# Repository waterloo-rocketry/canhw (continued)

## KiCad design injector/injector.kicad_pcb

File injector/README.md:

# Injector Board

This board is responsible for opening and closing the valve that allows for the nitrous oxide to flow into the engine before launch. It is designed to be able to deliver 10A of current to the injector valve. Limit switches mounted on the valve allow valve state to be determined.

The injector board is connected to the rocket CAN bus, through which it receives commands. The state of the injector valve is broadcast through the bus. The logic part of the board is powered from the bus, while the valve control portion is powered by an external lithium polymer battery.

## Front:

## Back:

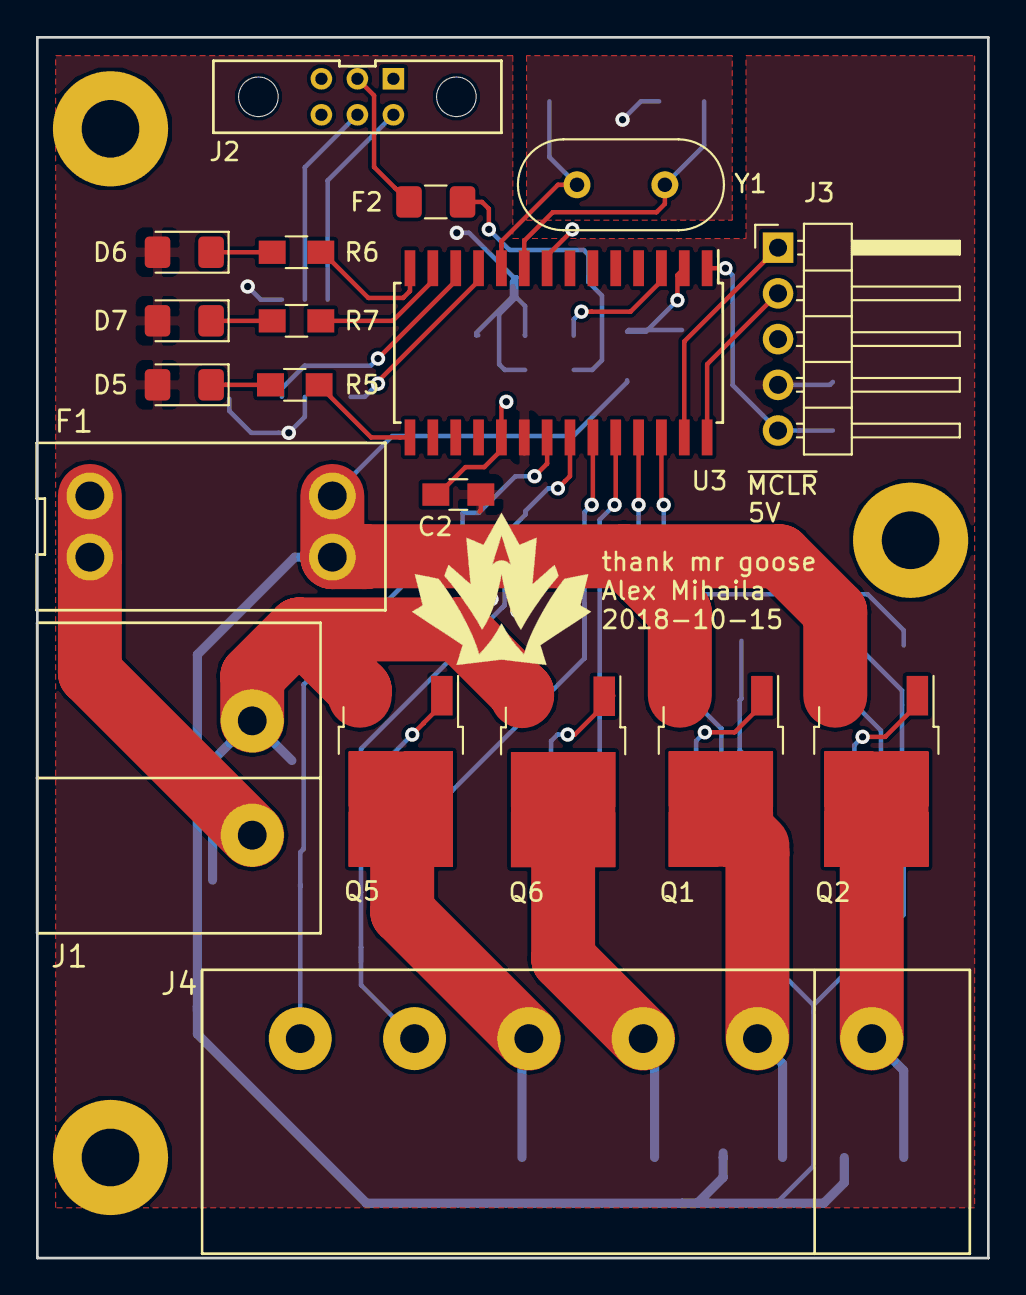
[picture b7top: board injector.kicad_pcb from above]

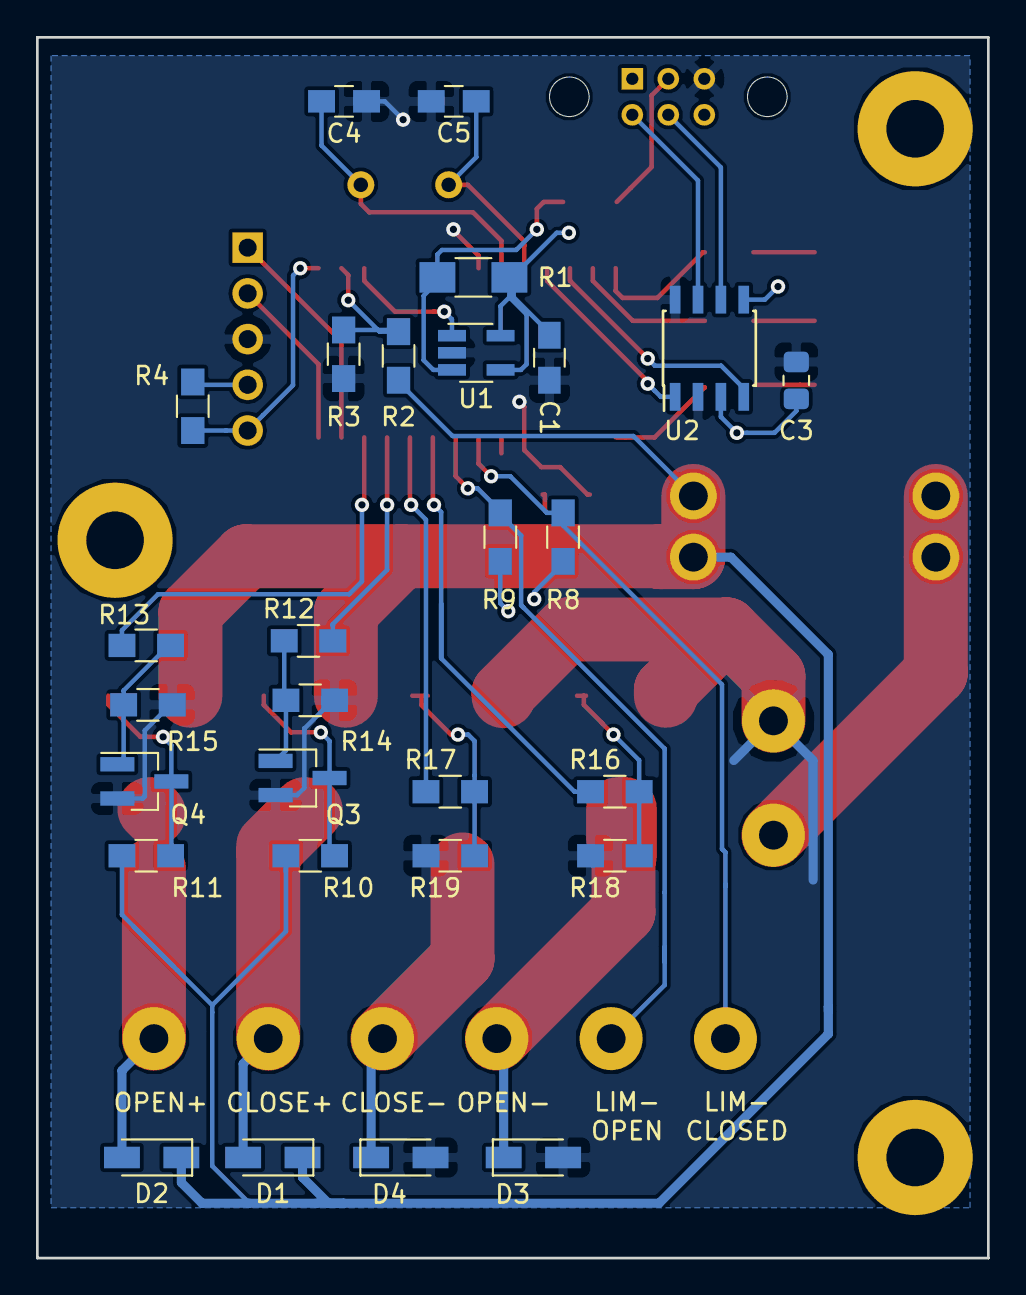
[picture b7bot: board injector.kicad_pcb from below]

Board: 2 copper layers, 52.8 x 67.8 mm, 47 parts (28 on the bottom side), 39 nets.

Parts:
C1, C2: 0.1uF; C_0805_HandSoldering
C3: 10uF; C_0805_2012Metric_Pad1.15x1.40mm_HandSolder
C4, C5: 26pF; C_0805_HandSoldering
D1, D2, D3, D4: BAS16GWJ; D_SOD-123_HandSoldering
D5, D6, D7: LED; LED_1206_3216Metric_Pad1.42x1.75mm_HandSolder
F1: 30A; PC_AutoFuse_Holder
F2: Polyfuse; Fuse_1206_3216Metric_Pad1.42x1.75mm_HandSolder
J1: Valve Power; Barrier_Strip_2Circuit
J2: CAN Connector; connector_Harwin_M80-5000642
J3: Programming Header; Pin_Header_Angled_1x05_Pitch2.54mm
J4: Valve Control; Barrier_Strip_6Circuit
Q1, Q2: AOD417; TO-252-2
Q3, Q4: DMG2302UK; SOT-23_Handsoldering
Q5, Q6: AOD476; TO-252-2
R1: 200mR; R_1206_HandSoldering
R2: 27K; R_0805_HandSoldering
R3, R4, R8, R9, R14, R15, R18, R19: 10K; R_0805_HandSoldering
R5, R6, R7: 330R; R_0805_HandSoldering
R10, R11: 15K; R_0805_HandSoldering
R12, R13, R16, R17: 270R; R_0805_HandSoldering
U1: INA180; SOT-23-5_HandSoldering
U2: MCP2562; SOIC-8_3.9x4.9mm_Pitch1.27mm
U3: PIC18F26K83; SOIC-28W_7.5x17.9mm_Pitch1.27mm
Y1: Crystal; Crystal_HC49-4H_Vertical

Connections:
+5V: C1.2, C2.2, C3.1, D5.2, D6.2, D7.2, J3.4, R1.1, R4.1, R8.1, R9.1, U1.4, U1.5, U2.3, U2.5, U3.20
+BATT: D1.1, D2.1, F1.2, Q1.3, Q2.3, R2.1, R10.1, R11.1
/MCU/CAN_RX: U2.4, U3.12
/MCU/CAN_TX: U2.1, U3.11
/MCU/CURR_AMP: U1.1, U3.3
/MCU/HIGH_SIDE_A: R12.2, U3.25
/MCU/HIGH_SIDE_B: R13.1, U3.26
/MCU/ICSPCLK: J3.1, U3.27
/MCU/ICSPDAT: J3.2, U3.28
/MCU/LIM_CLOSE: J4.6, R8.2, U3.21
/MCU/LIM_OPEN: J4.5, R9.2, U3.22
/MCU/LOW_SIDE_A: R16.2, U3.23
/MCU/LOW_SIDE_B: R17.1, U3.24
/MCU/OSC1: C4.1, U3.9, Y1.1
/MCU/OSC2: C5.1, U3.10, Y1.2
/MCU/VBAT: R2.2, R3.1, U3.2
/MCU/~MCLR: J3.5, R4.2, U3.1
/Motor Control/CLOSE+: D1.2, J4.2, Q1.2
/Motor Control/CLOSE-: D4.1, J4.3, Q6.2
/Motor Control/OPEN+: D2.2, J4.1, Q2.2
/Motor Control/OPEN-: D3.1, J4.4, Q5.2
CANH: J2.4, U2.7
CANL: J2.5, U2.6
GND: C1.1, C2.1, C3.2, C4.2, C5.2, D3.2, D4.2, J1.2, J2.3, J3.3, Q3.2, Q4.2, Q5.3, Q6.3, R3.2, R14.2, R15.2, R18.2, R19.2, U1.2, U2.2, U2.8, U3.8, U3.19
unnamed: D5.1, R5.1
unnamed: D6.1, R6.1
unnamed: D7.1, R7.1
unnamed: F1.1, J1.1
unnamed: F2.1, R1.2, U1.3
unnamed: F2.2, J2.2
unnamed: Q1.1, Q3.3, R10.2
unnamed: Q2.1, Q4.3, R11.2
unnamed: Q3.1, R12.1, R14.1
unnamed: Q4.1, R13.2, R15.1
unnamed: Q5.1, R16.1, R18.1
unnamed: Q6.1, R17.2, R19.1
unnamed: R5.2, U3.15
unnamed: R6.2, U3.14
unnamed: R7.2, U3.13

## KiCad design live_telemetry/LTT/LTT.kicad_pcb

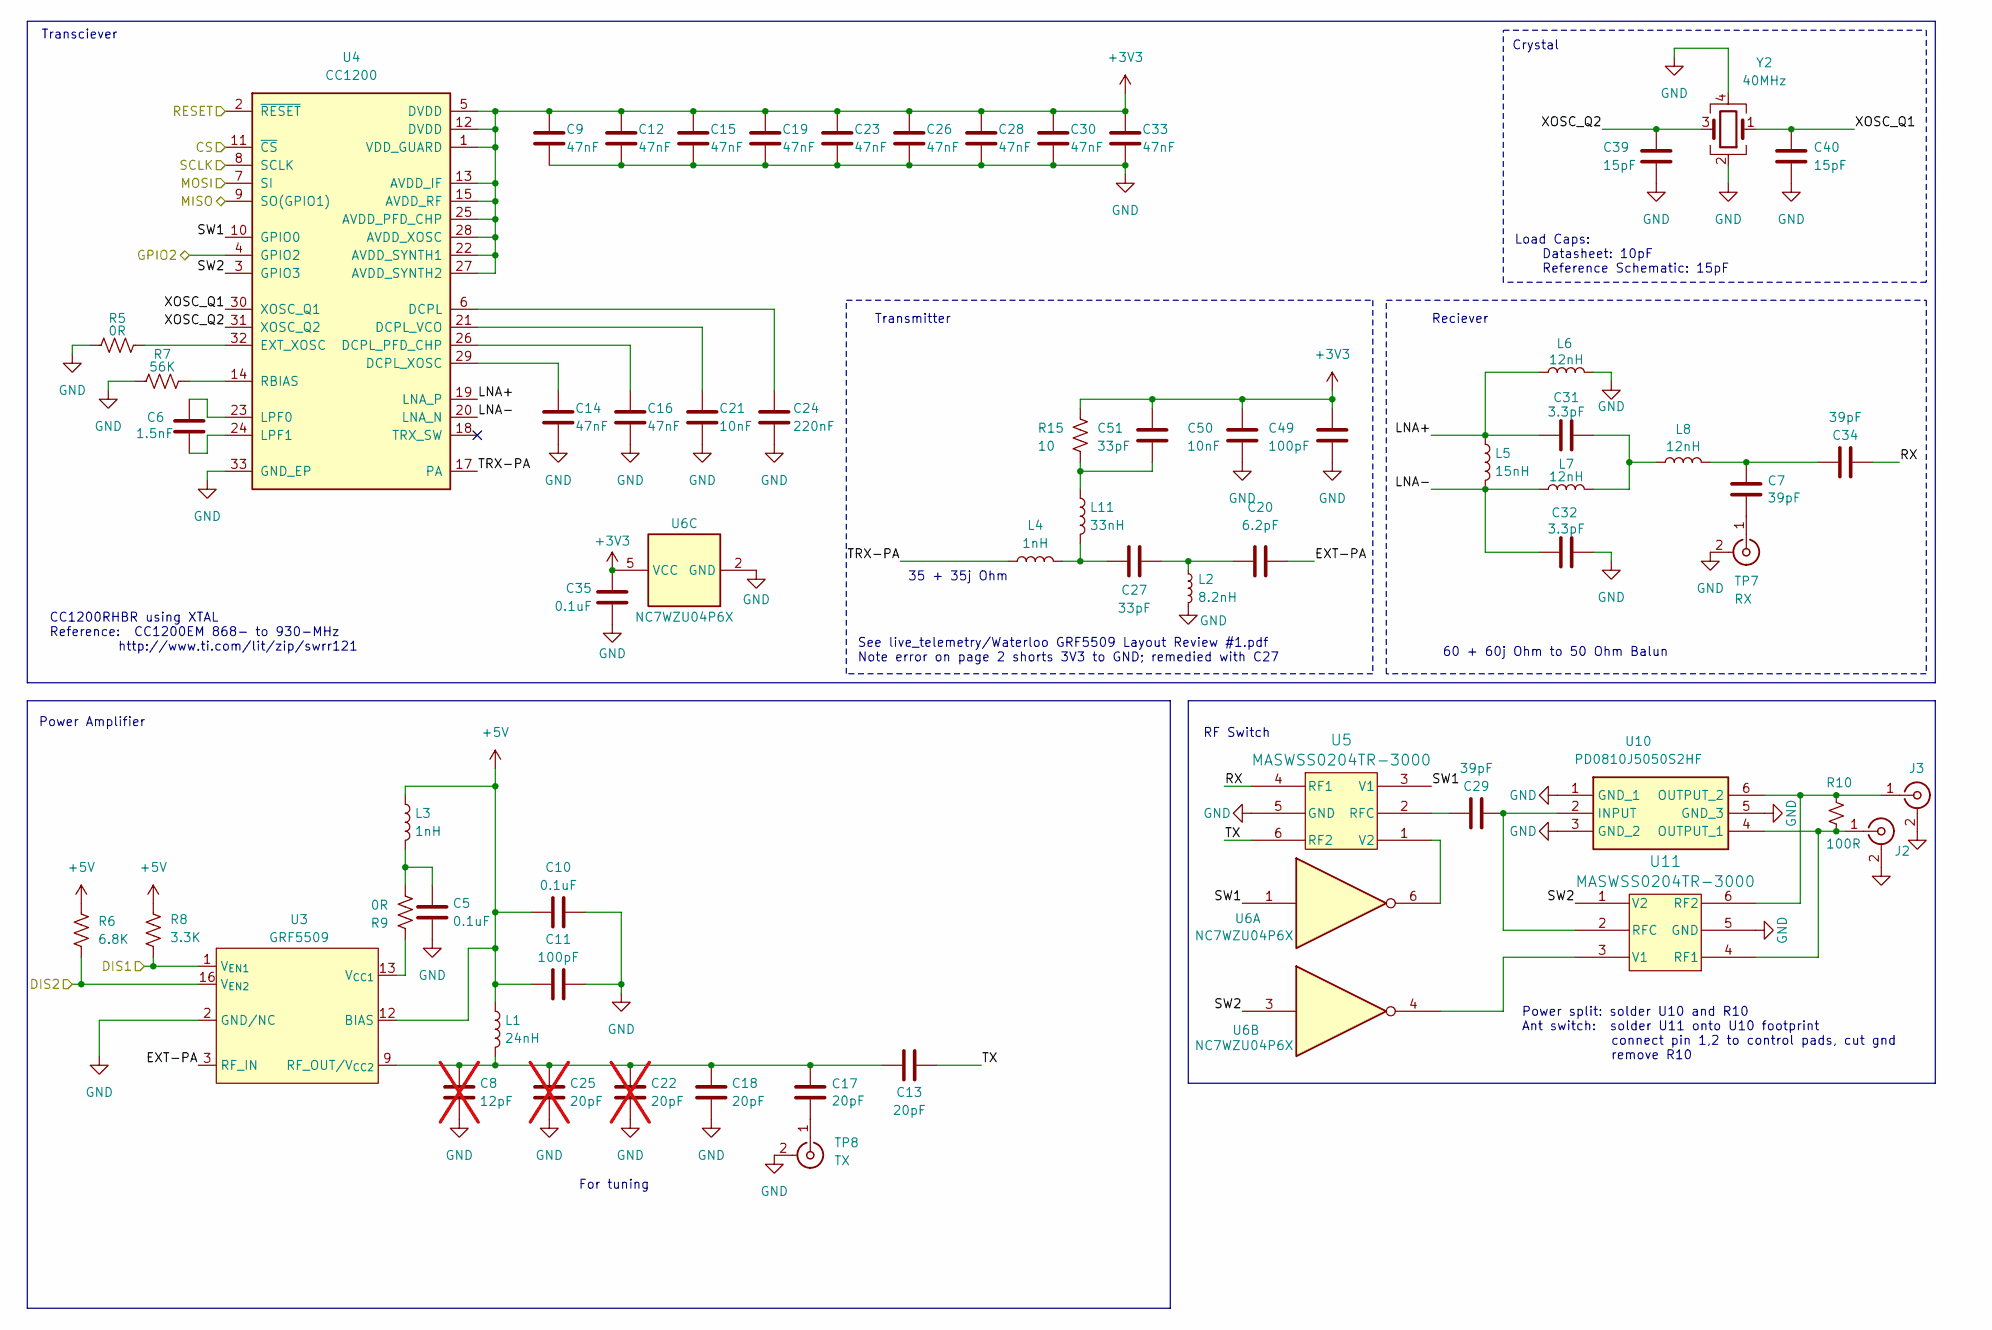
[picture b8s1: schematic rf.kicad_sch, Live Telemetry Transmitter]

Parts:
C5, C10, C35: 0.1uF; C_0402_1005Metric_Pad0.74x0.62mm_HandSolder
C6: 1.5nF; C_0402_1005Metric_Pad0.74x0.62mm_HandSolder
C7, C29, C34: 39pF; C_0402_1005Metric_Pad0.74x0.62mm_HandSolder
C8: 12pF; C_0402_1005Metric_Pad0.74x0.62mm_HandSolder; not fitted
C9, C12, C14, C15, C16, C19, C23, C26, C28, C30, C33: 47nF; C_0402_1005Metric_Pad0.74x0.62mm_HandSolder
C11, C49: 100pF; C_0402_1005Metric_Pad0.74x0.62mm_HandSolder
C13, C17, C18: 20pF; C_0402_1005Metric_Pad0.74x0.62mm_HandSolder
C20: 6.2pF; C_0402_1005Metric_Pad0.74x0.62mm_HandSolder
C21, C50: 10nF; C_0402_1005Metric_Pad0.74x0.62mm_HandSolder
C22, C25: 20pF; C_0402_1005Metric_Pad0.74x0.62mm_HandSolder; not fitted
C24: 220nF; C_0402_1005Metric_Pad0.74x0.62mm_HandSolder
C27, C51: 33pF; C_0402_1005Metric_Pad0.74x0.62mm_HandSolder
C31, C32: 3.3pF; C_0402_1005Metric_Pad0.74x0.62mm_HandSolder
C39, C40: 15pF; C_0402_1005Metric_Pad0.74x0.62mm_HandSolder
J2, J3: Conn_Coaxial; SMA_Samtec_SMA-J-P-H-ST-EM1_EdgeMount
L1: 24nH; L_0402_1005Metric_Pad0.77x0.64mm_HandSolder
L2: 8.2nH; L_0402_1005Metric_Pad0.77x0.64mm_HandSolder
L3, L4: 1nH; L_0402_1005Metric_Pad0.77x0.64mm_HandSolder
L5: 15nH; L_0402_1005Metric_Pad0.77x0.64mm_HandSolder
L6, L7, L8: 12nH; L_0402_1005Metric_Pad0.77x0.64mm_HandSolder
L11: 33nH; L_0402_1005Metric_Pad0.77x0.64mm_HandSolder
R5, R9: 0R; R_0402_1005Metric_Pad0.72x0.64mm_HandSolder
R6: 6.8K; R_0402_1005Metric_Pad0.72x0.64mm_HandSolder
R7: 56K; R_0402_1005Metric_Pad0.72x0.64mm_HandSolder
R8: 3.3K; R_0402_1005Metric_Pad0.72x0.64mm_HandSolder
R10: 100R; R_0603_1608Metric_Pad0.98x0.95mm_HandSolder
R15: 10; R_0402_1005Metric_Pad0.72x0.64mm_HandSolder
TP7: RX; U.FL_Molex_MCRF_73412-0110_Vertical
TP8: TX; U.FL_Molex_MCRF_73412-0110_Vertical
U3: GRF5509; QFN50P300X300X85-17N
U4: CC1200; QFN-32-1EP_5x5mm_P0.5mm_EP3.45x3.45mm
U5, U11: MASWSS0204TR-3000; SOT-363_1P25X2_MCM
U6: NC7WZU04P6X; SOT-363_SC-70-6_Handsoldering
U10: PD0810J5050S2HF; Manufacturer_Part_Number PD0810J5050S2HF
Y2: 40MHz; Crystal_SMD_3225-4Pin_3.2x2.5mm

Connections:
+3V3: C9.1, C12.1, C15.1, C19.1, C23.1, C26.1, C28.1, C30.1, C33.1, C35.1, C49.1, C50.1, C51.1, R15.1, U4.1 (VDD_GUARD), U4.5 (DVDD), U4.12 (DVDD), U4.13 (AVDD_IF), U4.15 (AVDD_RF), U4.22 (AVDD_SYNTH1), U4.25 (AVDD_PFD_CHP), U4.27 (AVDD_SYNTH2), U4.28 (AVDD_XOSC), U6.5 (VCC); also elsewhere on the board
+5V: C10.1, C11.1, L1.1, L3.1, R6.1, R8.1, U3.12 (BIAS); also elsewhere on the board
/MCU/CS: U4.11 (~CS); also elsewhere on the board
/MCU/DIS1: R8.2, U3.1 (V_{EN1}); also elsewhere on the board
/MCU/DIS2: R6.2, U3.16 (V_{EN2}); also elsewhere on the board
/MCU/GPIO2: U4.4 (GPIO2); also elsewhere on the board
/MCU/MISO: U4.9 (SO(GPIO1)); also elsewhere on the board
/MCU/MOSI: U4.7 (SI); also elsewhere on the board
/MCU/RESET: U4.2 (~RESET); also elsewhere on the board
/MCU/SCLK: U4.8 (SCLK); also elsewhere on the board
/RF/EXT-PA: C20.2, U3.3 (RF_IN), U3.4 (RF_IN)
/RF/LNA+: C31.1, L5.1, L6.1, U4.19 (LNA_P)
/RF/LNA-: C32.1, L5.2, L7.1, U4.20 (LNA_N)
/RF/RX: C34.2, U5.4 (RF1)
/RF/SW1: U4.10 (GPIO0), U5.3 (V1), U6.1
/RF/SW2: U4.3 (GPIO3), U6.3, U11.1 (V2)
/RF/TRX-PA: L4.1, U4.17 (PA)
/RF/TX: C13.2, U5.6 (RF2)
/RF/XOSC_Q1: C40.1, U4.30 (XOSC_Q1), Y2.1
/RF/XOSC_Q2: C39.1, U4.31 (XOSC_Q2), Y2.3
GND: C5.2, C8.2, C9.2, C10.2, C11.2, C12.2, C14.2, C15.2, C16.2, C18.2, C19.2, C21.2, C22.2, C23.2, C24.2, C25.2, C26.2, C28.2, C30.2, C32.2, C33.2, C35.2, C39.2, C40.2, C49.2, C50.2, J2.2 (Ext), J3.2 (Ext), L2.2, L6.2, R5.1, R7.1, TP7.2 (Ext), TP8.2 (Ext), U3.2 (GND/NC), U3.5 (GND/NC), U3.6 (GND/NC), U3.7 (GND/NC), U3.8 (GND/NC), U3.11 (GND/NC), U3.14 (GND/NC), U3.15 (GND/NC), U4.33 (GND_EP), U5.5 (GND), U6.2 (GND), U10.1 (GND_1), U10.3 (GND_2), U10.5 (GND_3), U11.5 (GND), Y2.2, Y2.4; also elsewhere on the board
unnamed: C5.1, L3.2, R9.2
unnamed: C8.1, C13.1, C17.1, C18.1, C22.1, C25.1, L1.2, U3.9 (RF_OUT/V_{CC2}), U3.10 (RF_OUT/V_{CC2})
unnamed: C20.1, C27.1, L2.1
unnamed: C27.2, L4.2, L11.2
unnamed: C31.2, L7.2, L8.1
unnamed: C7.1, C34.1, L8.2
unnamed: C51.2, L11.1, R15.2
unnamed: J2.1 (In), R10.2, U10.4 (OUTPUT_1), U11.4 (RF1)
unnamed: J3.1 (In), R10.1, U10.6 (OUTPUT_2), U11.6 (RF2)
unnamed: C7.2, TP7.1 (In)
unnamed: C17.2, TP8.1 (In)
unnamed: R9.1, U3.13 (V_{CC1})
unnamed: C24.1, U4.6 (DCPL)
unnamed: C16.1, U4.26 (DCPL_PFD_CHP)
unnamed: C21.1, U4.21 (DCPL_VCO)
unnamed: C14.1, U4.29 (DCPL_XOSC)
unnamed: R5.2, U4.32 (EXT_XOSC)
unnamed: C6.1, U4.23 (LPF0)
unnamed: C6.2, U4.24 (LPF1)
unnamed: R7.2, U4.14 (RBIAS)
unnamed: C29.1, U5.2 (RFC)
unnamed: U5.1 (V2), U6.6
unnamed: U6.4, U11.3 (V1)
unnamed: C29.2, U10.2 (INPUT), U11.2 (RFC)

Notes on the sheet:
Transciever
Load Caps: Datasheet: 10pF Reference Schematic: 15pF
Power Amplifier
RF Switch
CC1200RHBR using XTAL Reference: CC1200EM 868- to 930-MHz http://www.ti.com/lit/zip/swrr121
Power split: solder U10 and R10 Ant switch: solder U11 onto U10 footprint connect pin 1,2 to control pads, cut gnd remove R10
35 + 35j Ohm
Crystal
60 + 60j Ohm to 50 Ohm Balun
Transmitter
See live_telemetry/Waterloo GRF5509 Layout Review #1.pdf Note error on page 2 shorts 3V3 to GND; remedied with C27
Reciever
For tuning

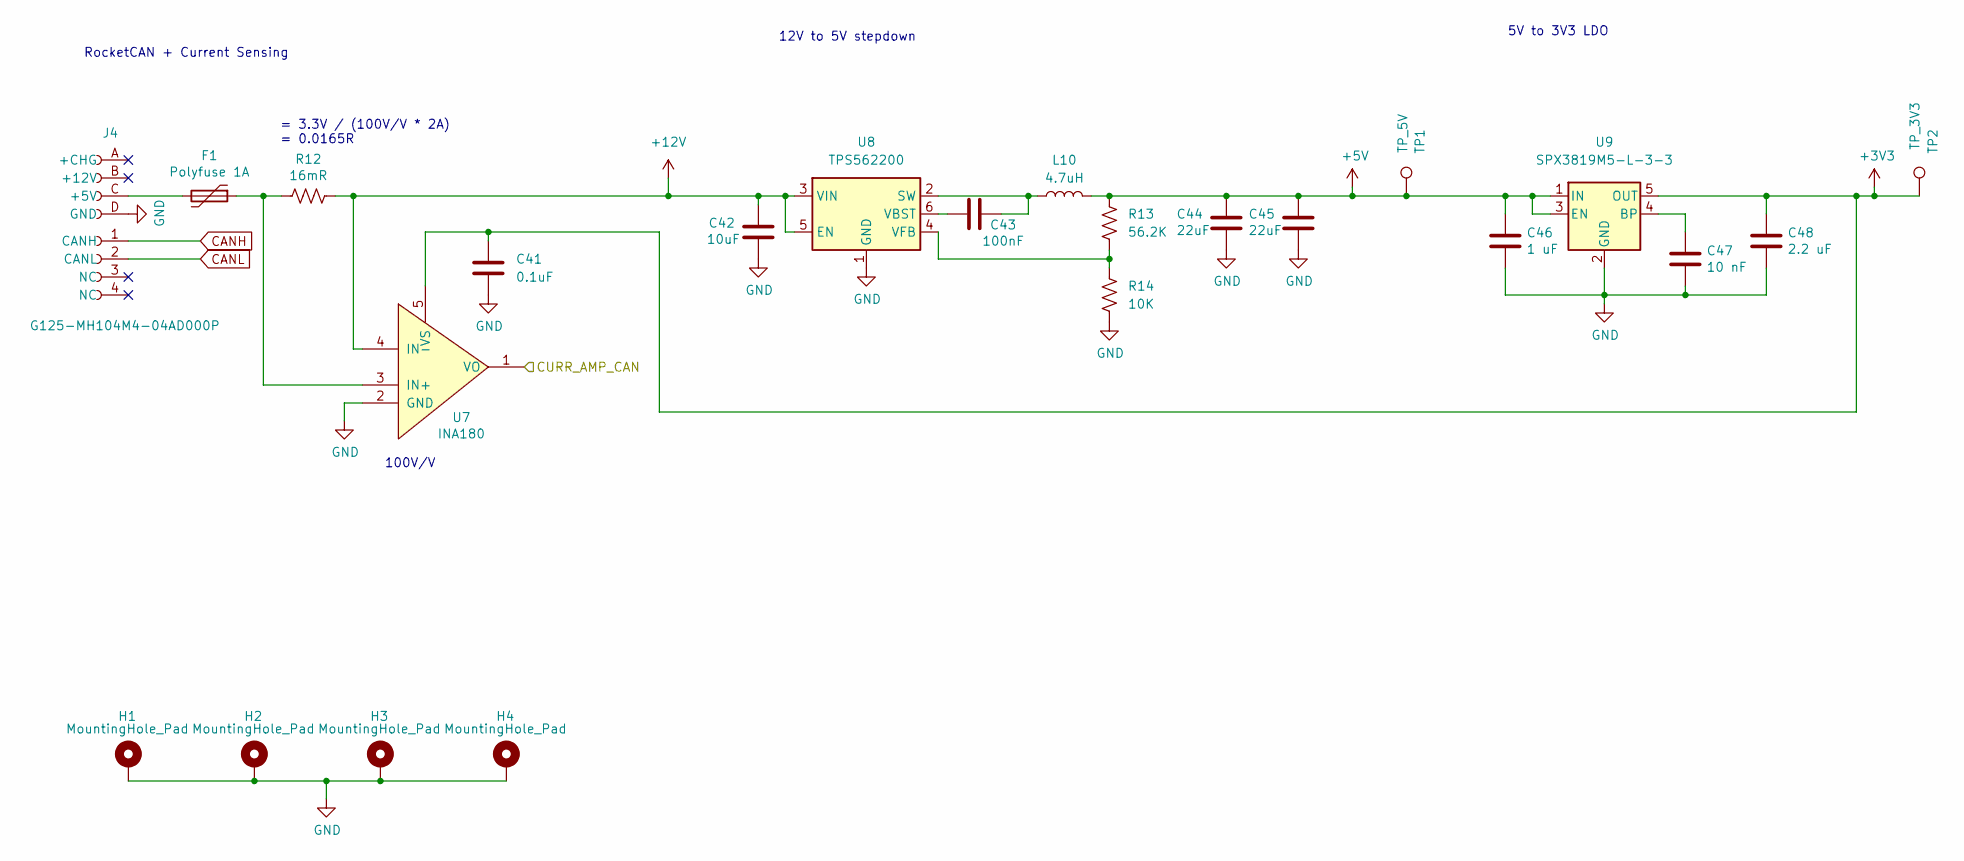
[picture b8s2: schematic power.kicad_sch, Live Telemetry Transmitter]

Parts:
C41: 0.1uF; C_0805_2012Metric_Pad1.18x1.45mm_HandSolder
C42: 10uF; C_0805_2012Metric_Pad1.18x1.45mm_HandSolder
C43: 100nF; C_0805_2012Metric_Pad1.18x1.45mm_HandSolder
C44, C45: 22uF; C_0603_1608Metric_Pad1.08x0.95mm_HandSolder
C46: 1 uF; C_0805_2012Metric_Pad1.18x1.45mm_HandSolder
C47: 10 nF; C_0805_2012Metric_Pad1.18x1.45mm_HandSolder
C48: 2.2 uF; C_0805_2012Metric_Pad1.18x1.45mm_HandSolder
F1: Polyfuse 1A; Fuse_1206_3216Metric_Pad1.42x1.75mm_HandSolder
H1, H2, H3, H4: MountingHole_Pad; MountingHole_3.2mm_M3_Pad_Via
J4: G125-MH104M4-04AD000P; connector_Harwin_G125-MH104M4-04AD000P
L10: 4.7uH; L_Bourns-SRN8040_8x8.15mm
R12: 16mR; R_0805_2012Metric_Pad1.20x1.40mm_HandSolder
R13: 56.2K; R_0805_2012Metric_Pad1.20x1.40mm_HandSolder
R14: 10K; R_0805_2012Metric_Pad1.20x1.40mm_HandSolder
TP1: TP_5V; TestPoint_Pad_D3.0mm
TP2: TP_3V3; TestPoint_Pad_D3.0mm
U7: INA180; SOT-23-5_HandSoldering
U8: TPS562200; SOT-23-6
U9: SPX3819M5-L-3-3; SOT-23-5

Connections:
+3V3: C41.1, C48.1, TP2.1, U7.5 (VS), U9.5 (OUT); also elsewhere on the board
+5V: C44.1, C45.1, C46.1, L10.2, R13.1, TP1.1, U9.1 (IN), U9.3 (EN); also elsewhere on the board
+12V: C42.1, R12.1, U7.4 (IN-), U8.3 (VIN), U8.5 (EN)
/MCU/CURR_AMP_CAN: U7.1 (VO); also elsewhere on the board
CANH: J4.1 (CANH); also elsewhere on the board
CANL: J4.2 (CANL); also elsewhere on the board
GND: C41.2, C42.2, C44.2, C45.2, C46.2, C47.2, C48.2, H1.1, H2.1, H3.1, H4.1, J4.D (GND), R14.2, U7.2 (GND), U8.1 (GND), U9.2 (GND); also elsewhere on the board
unnamed: F1.2, J4.C (+5V)
unnamed: F1.1, R12.2, U7.3 (IN+)
unnamed: C43.1, L10.1, U8.2 (SW)
unnamed: C43.2, U8.6 (VBST)
unnamed: R13.2, R14.1, U8.4 (VFB)
unnamed: C47.1, U9.4 (BP)

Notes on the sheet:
100V/V
RocketCAN + Current Sensing
= 3.3V / (100V/V * 2A) = 0.0165R
5V to 3V3 LDO
12V to 5V stepdown

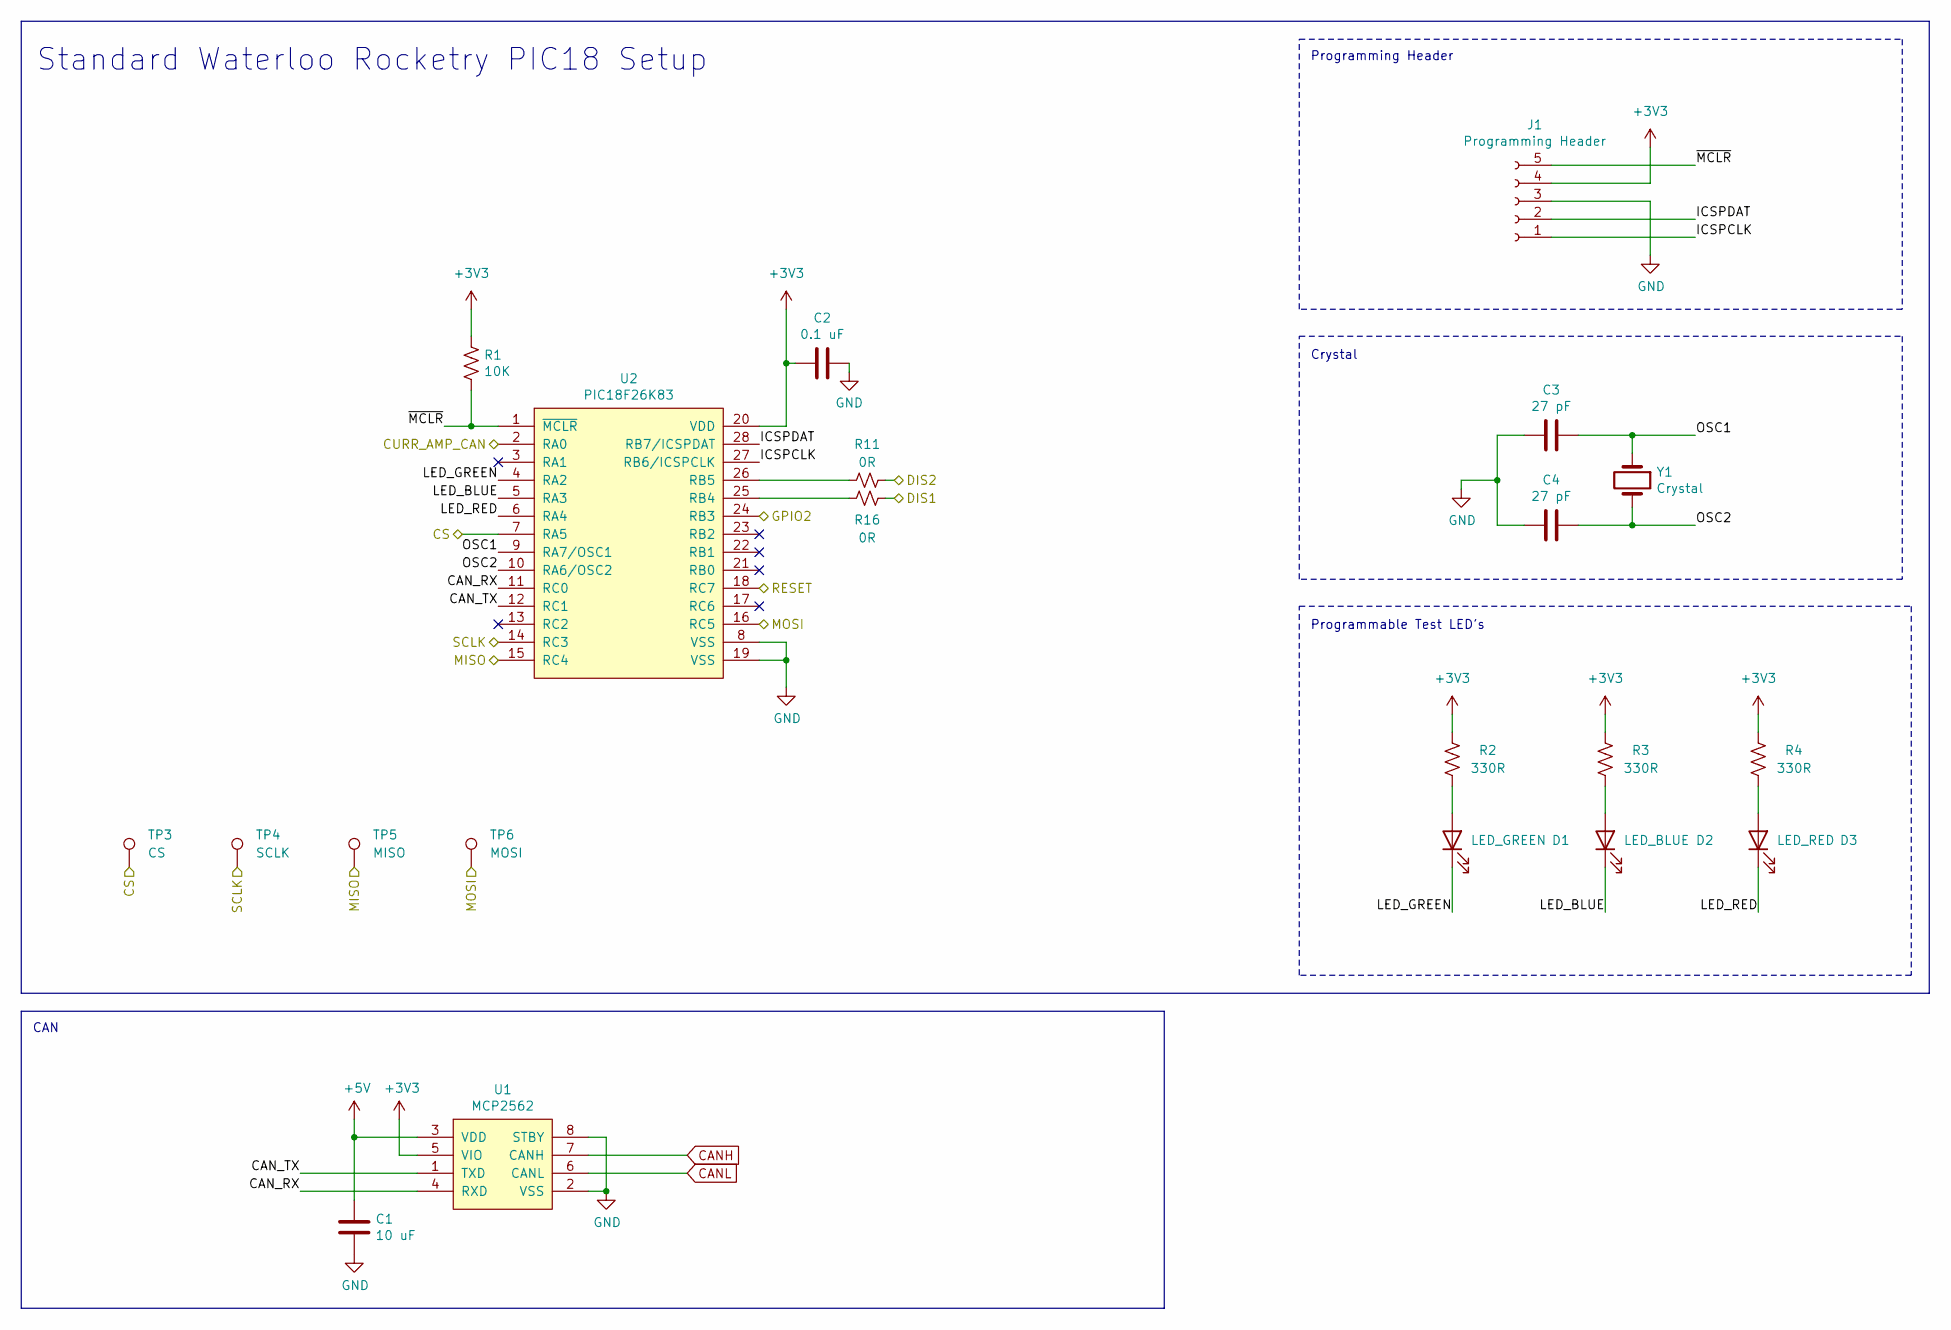
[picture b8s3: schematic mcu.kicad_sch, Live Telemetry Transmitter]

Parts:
C1: 10 uF; C_0603_1608Metric_Pad1.08x0.95mm_HandSolder
C2: 0.1 uF; C_0603_1608Metric_Pad1.08x0.95mm_HandSolder
C3, C4: 27 pF; C_0603_1608Metric_Pad1.08x0.95mm_HandSolder
D1: LED_GREEN; LED_1206_3216Metric_Pad1.42x1.75mm_HandSolder
D2: LED_BLUE; LED_1206_3216Metric_Pad1.42x1.75mm_HandSolder
D3: LED_RED; LED_1206_3216Metric_Pad1.42x1.75mm_HandSolder
J1: Programming Header; PinSocket_5x2.54_SMD_90deg_952-3198-1-ND
R1: 10K; R_0603_1608Metric_Pad0.98x0.95mm_HandSolder
R2, R3, R4: 330R; R_0603_1608Metric_Pad0.98x0.95mm_HandSolder
R11, R16: 0R; R_0402_1005Metric_Pad0.72x0.64mm_HandSolder
TP3: CS; TestPoint_Pad_D1.0mm
TP4: SCLK; TestPoint_Pad_D1.0mm
TP5: MISO; TestPoint_Pad_D1.0mm
TP6: MOSI; TestPoint_Pad_D1.0mm
U1: MCP2562; SOIC-8_3.9x4.9mm_P1.27mm
U2: PIC18F26K83; SOIC-28W_7.5x17.9mm_P1.27mm
Y1: Crystal; Resonator-2Pin_W10.0mm_H5.0mm

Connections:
+3V3: C2.2, J1.4, R1.1, R2.2, R3.2, R4.2, U1.5 (VIO), U2.20 (VDD); also elsewhere on the board
+5V: C1.1, U1.3 (VDD); also elsewhere on the board
/MCU/CAN_RX: U1.4 (RXD), U2.11 (RC0)
/MCU/CAN_TX: U1.1 (TXD), U2.12 (RC1)
/MCU/CS: TP3.1, U2.7 (RA5); also elsewhere on the board
/MCU/CURR_AMP_CAN: U2.2 (RA0); also elsewhere on the board
/MCU/DIS1: R16.1; also elsewhere on the board
/MCU/DIS2: R11.2; also elsewhere on the board
/MCU/GPIO2: U2.24 (RB3); also elsewhere on the board
/MCU/ICSPCLK: J1.1, U2.27 (RB6/ICSPCLK)
/MCU/ICSPDAT: J1.2, U2.28 (RB7/ICSPDAT)
/MCU/LED_BLUE: D2.1 (K), U2.5 (RA3)
/MCU/LED_GREEN: D1.1 (K), U2.4 (RA2)
/MCU/LED_RED: D3.1 (K), U2.6 (RA4)
/MCU/MISO: TP5.1, U2.15 (RC4); also elsewhere on the board
/MCU/MOSI: TP6.1, U2.16 (RC5); also elsewhere on the board
/MCU/OSC1: C3.1, U2.9 (RA7/OSC1), Y1.1
/MCU/OSC2: C4.1, U2.10 (RA6/OSC2), Y1.2
/MCU/RESET: U2.18 (RC7); also elsewhere on the board
/MCU/SCLK: TP4.1, U2.14 (RC3); also elsewhere on the board
/MCU/~MCLR: J1.5, R1.2, U2.1 (~MCLR)
CANH: U1.7 (CANH); also elsewhere on the board
CANL: U1.6 (CANL); also elsewhere on the board
GND: C1.2, C2.1, C3.2, C4.2, J1.3, U1.2 (VSS), U1.8 (STBY), U2.8 (VSS), U2.19 (VSS); also elsewhere on the board
unnamed: D1.2 (A), R2.1
unnamed: D2.2 (A), R3.1
unnamed: D3.2 (A), R4.1
unnamed: R16.2, U2.25 (RB4)
unnamed: R11.1, U2.26 (RB5)

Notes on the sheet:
CAN
Crystal
Programming Header
Standard Waterloo Rocketry PIC18 Setup
Programmable Test LED's

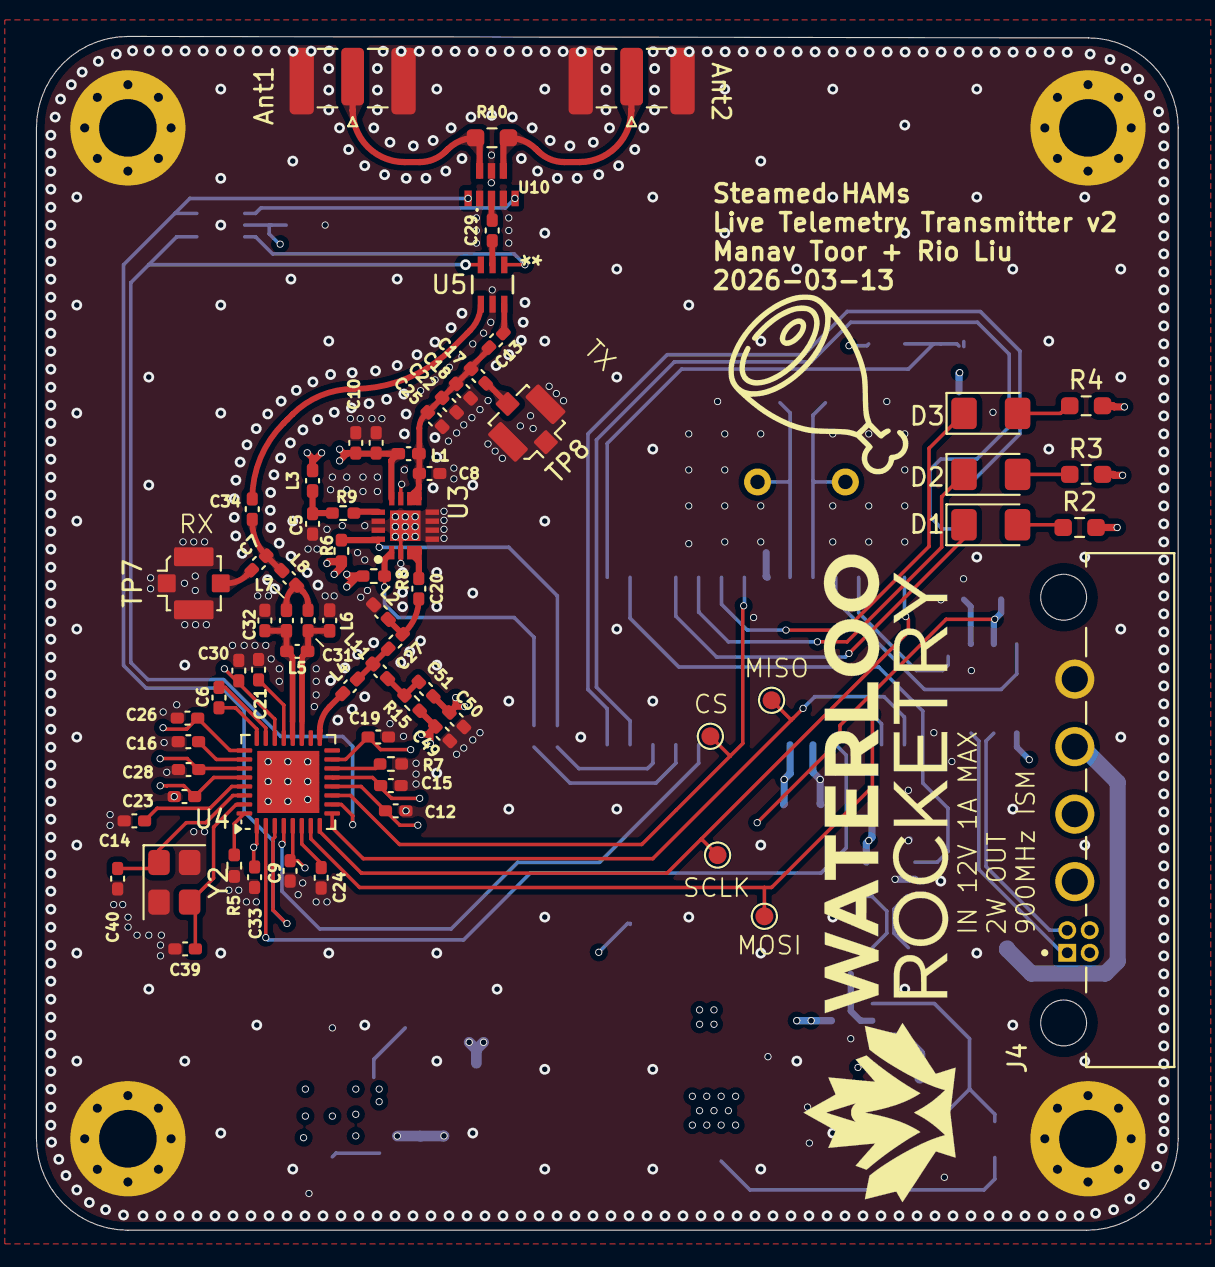
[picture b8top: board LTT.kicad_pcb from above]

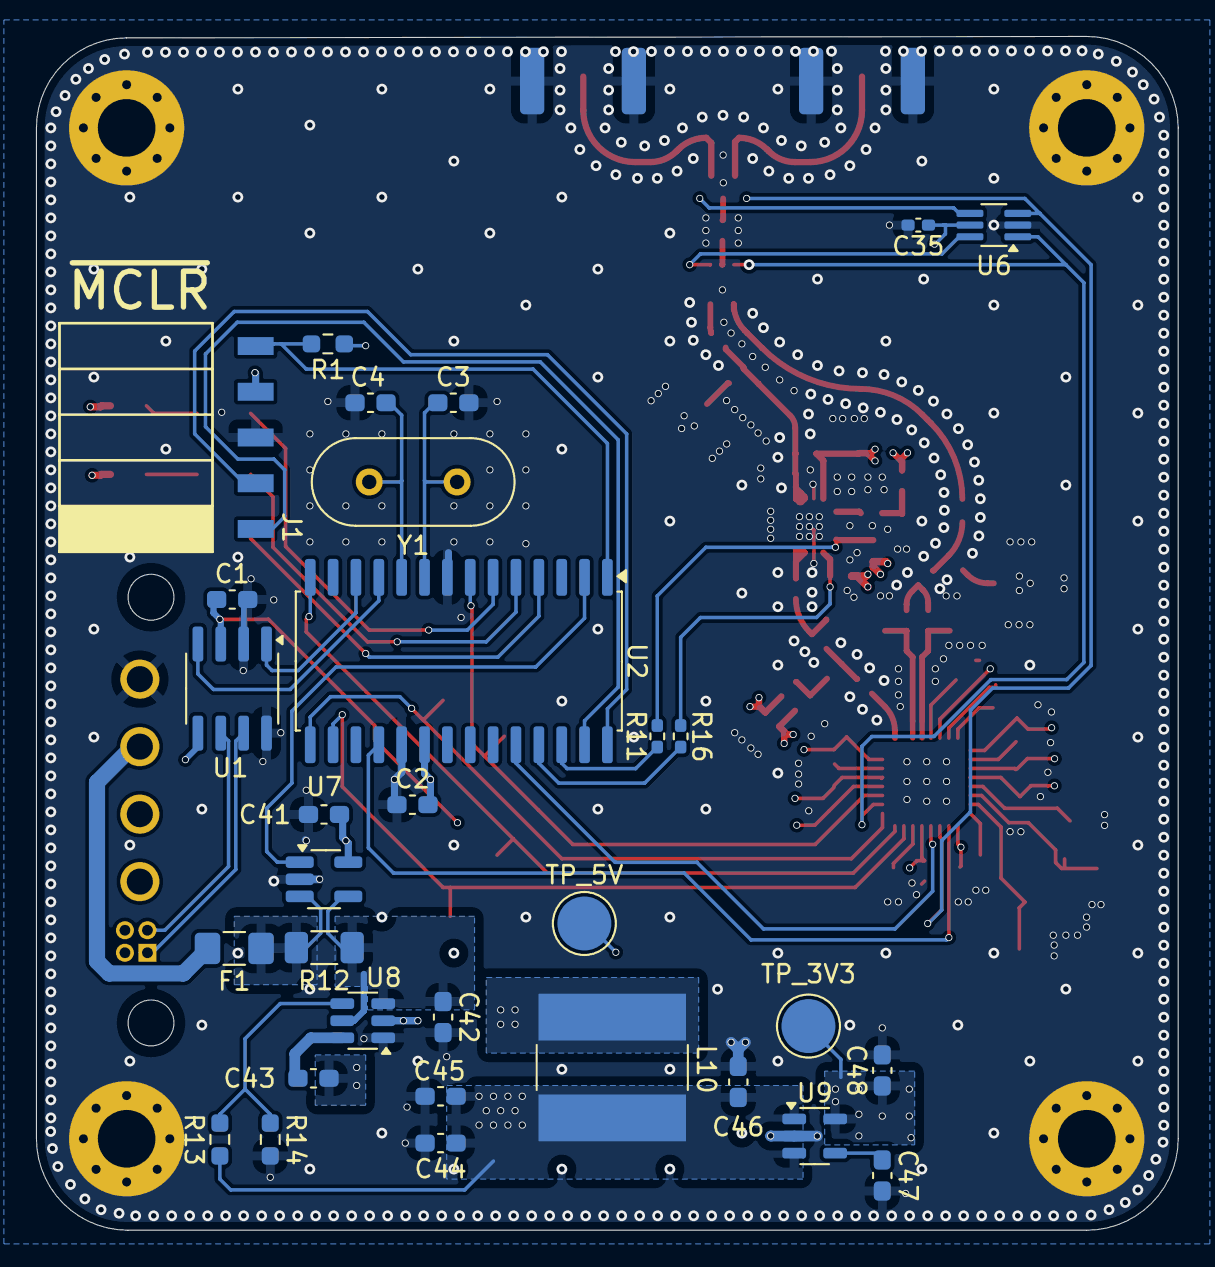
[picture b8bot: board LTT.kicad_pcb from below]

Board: 4 copper layers, 63.4 x 66.3 mm, 106 parts (31 on the bottom side), 69 nets.

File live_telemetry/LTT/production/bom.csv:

Designator,Footprint,Quantity,Value,LCSC Part #
"_2, ",,2,,
C1,0603,1,10 uF,
"C10, C35, C5",0402,3,0.1uF,
"C11, C49",0402,2,100pF,
"C12, C14, C15, C16, C19, C23, C26, C28, C30, C33, C9",0402,11,47nF,
"C13, C17, C18",0402,3,20pF,
C2,0603,1,0.1 uF,
C20,0402,1,6.2pF,
"C21, C50",0402,2,10nF,
C24,0402,1,220nF,
"C27, C51",0402,2,33pF,
"C29, C34, C7",0402,3,39pF,
"C3, C4",0603,2,27 pF,
"C31, C32",0402,2,3.3pF,
"C39, C40",0402,2,15pF,
C41,0603,1,0.1uF,
C42,0603,1,10uF,
C43,0603,1,100nF,
"C44, C45",0603,2,22uF,
C46,0603,1,1 uF,
C47,0603,1,10 nF,
C48,0603,1,2.2 uF,
C6,0402,1,1.5nF,
D1,1206,1,LED_GREEN,
D2,1206,1,LED_BLUE,
D3,1206,1,LED_RED,
F1,1206,1,Polyfuse 1A,
J1,PinSocket_5x2.54_SMD_90deg_952-3198-1-ND,1,Programming Header,
"J2, J3",SMA_Samtec_SMA-J-P-H-ST-EM1_EdgeMount,2,Conn_Coaxial,
J4,connector_Harwin_G125-MH104M4-04AD000P,1,G125-MH104M4-04AD000P,
L1,0402,1,24nH,
L10,L_Bourns-SRN8040_8x8.15mm,1,4.7uH,
L11,0402,1,33nH,
L2,0402,1,8.2nH,
"L3, L4",0402,2,1nH,
L5,0402,1,15nH,
"L6, L7, L8",0402,3,12nH,
"R1, R14",0603,2,10K,
R10,0603,1,100R,
"R11, R16, R5, R9",0402,4,0R,
R12,1206,1,16mR,
R13,0603,1,56.2K,
R15,0402,1,10,
"R2, R3, R4",0603,3,330R,
R6,0402,1,6.8K,
R7,0402,1,56K,
R8,0402,1,3.3K,
TP1,TestPoint_Pad_D3.0mm,1,TP_5V,
TP2,TestPoint_Pad_D3.0mm,1,TP_3V3,
TP3,TestPoint_Pad_D1.0mm,1,CS,
TP4,TestPoint_Pad_D1.0mm,1,SCLK,
TP5,TestPoint_Pad_D1.0mm,1,MISO,
TP6,TestPoint_Pad_D1.0mm,1,MOSI,
TP7,U.FL_Molex_MCRF_73412-0110_Vertical,1,RX,
TP8,U.FL_Molex_MCRF_73412-0110_Vertical,1,TX,
U1,SOIC-8_3.9x4.9mm_P1.27mm,1,MCP2562,
U10,PD0810J5050S2HF,1,PD0810J5050S2HF,
U2,SOIC-28W_7.5x17.9mm_P1.27mm,1,PIC18F26K83,
U3,QFN50P300X300X85-17N,1,GRF5509,
U4,QFN-32-1EP_5x5mm_P0.5mm_EP3.45x3.45mm,1,CC1200,
U5,SOT-363_1P25X2_MCM,1,MASWSS0204TR-3000,
U6,SOT-363_SC-70-6_Handsoldering,1,NC7WZU04P6X,
U7,SOT-23-5_HandSoldering,1,INA180,
U8,SOT-23-6,1,TPS562200,
U9,SOT-23-5,1,SPX3819M5-L-3-3,
Y1,Crystal_HC49-4H_Vertical,1,Crystal,
Y2,Crystal_SMD_3225-4Pin_3.2x2.5mm,1,40MHz,
